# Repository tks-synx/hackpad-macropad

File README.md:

# hackpad-macropad

## Design Renders & Screenshots

### Macropad Design (Fusion)

(Was not able to get the actual models for keycaps, switches, the OLED, rotator or MCU in Fusion)

### 3D Case Design (Fusion)

### Circuit Schematic (KiCad)

### PCB Layout (KiCad)

## Bill of Materials (BOM)
* [1]x Seeed XIAO RP2040 microcontroller
* [10]x MX-style mechanical switches
* [10]x Blank DSA keycaps
* [1]x 0.91” 128×32 OLED display 
* [1]x EC11 rotary encoders
* [4]x M3×16mm screws
* [4]x M3×5×4mm heatset inserts 
* 3D Printing Filament (PLA/PETG) In colour if possible

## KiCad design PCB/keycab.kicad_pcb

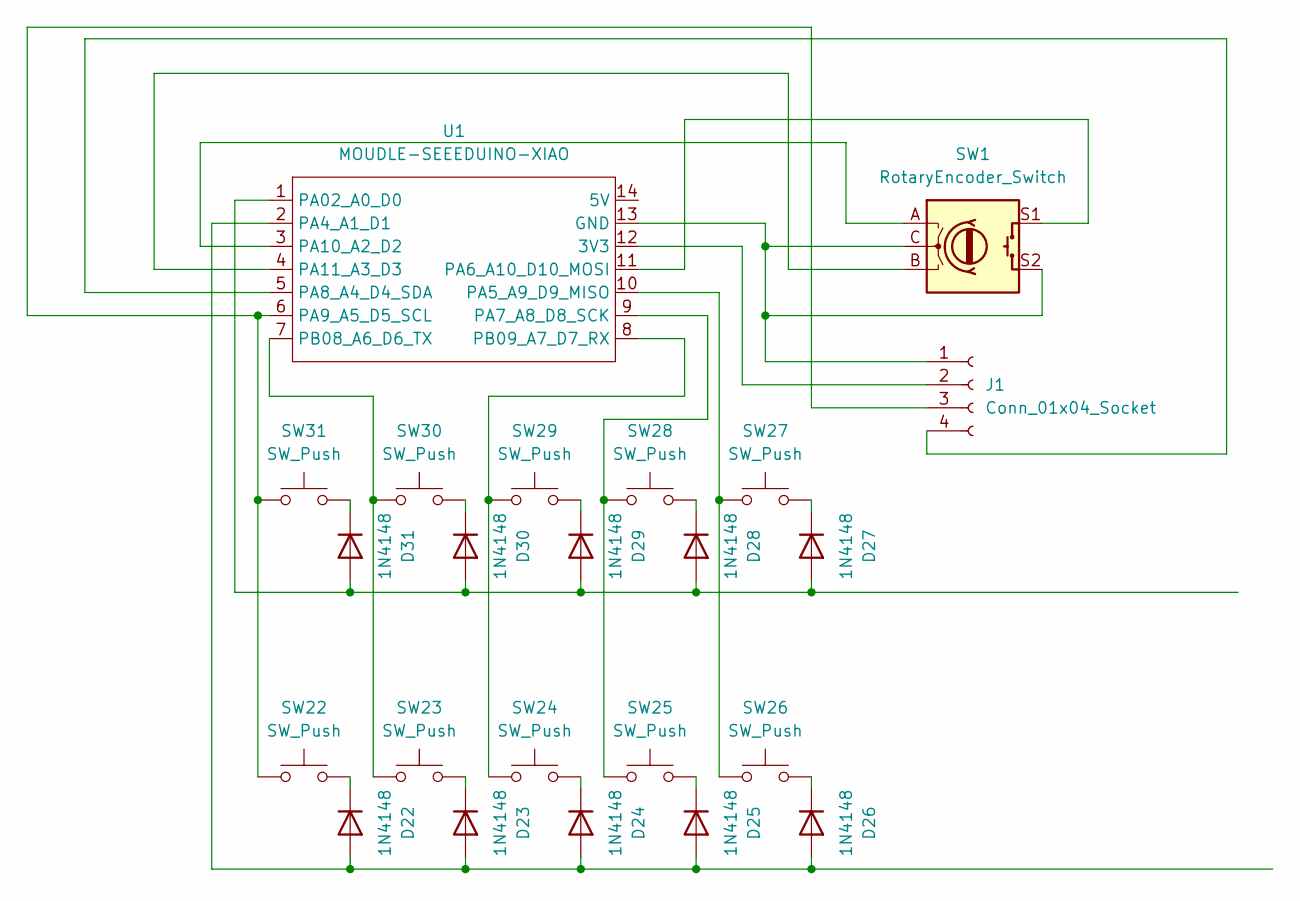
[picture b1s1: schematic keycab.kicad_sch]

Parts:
D22, D23, D24, D25, D26, D27, D28, D29, D30, D31: 1N4148; D_DO-35_SOD27_P7.62mm_Horizontal
J1: Conn_01x04_Socket; PinHeader_1x04_P2.54mm_Vertical
SW1: RotaryEncoder_Switch; RotaryEncoder_Alps_EC11E-Switch_Vertical_H20mm
SW22, SW23, SW24, SW25, SW26, SW27, SW28, SW29, SW30, SW31: SW_Push; SW_Cherry_MX_1.00u_PCB
U1: MOUDLE-SEEEDUINO-XIAO; XIAO-Generic-Hybrid-14P-2.54-21X17.8MM

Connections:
unnamed: D22.2 (A), D23.2 (A), D24.2 (A), D25.2 (A), D26.2 (A), U1.2 (PA4_A1_D1)
unnamed: D22.1 (K), SW22.2
unnamed: D23.1 (K), SW23.2
unnamed: D24.1 (K), SW24.2
unnamed: D25.1 (K), SW25.2
unnamed: D26.1 (K), SW26.2
unnamed: D27.2 (A), D28.2 (A), D29.2 (A), D30.2 (A), D31.2 (A), U1.1 (PA02_A0_D0)
unnamed: D27.1 (K), SW27.2
unnamed: D28.1 (K), SW28.2
unnamed: D29.1 (K), SW29.2
unnamed: D30.1 (K), SW30.2
unnamed: D31.1 (K), SW31.2
unnamed: J1.1, SW1.C, SW1.S2, U1.13 (GND)
unnamed: J1.2, U1.12 (3V3)
unnamed: J1.3, SW22.1, SW31.1, U1.6 (PA9_A5_D5_SCL)
unnamed: J1.4, U1.5 (PA8_A4_D4_SDA)
unnamed: SW26.1, SW27.1, U1.10 (PA5_A9_D9_MISO)
unnamed: SW1.S1, U1.11 (PA6_A10_D10_MOSI)
unnamed: SW25.1, SW28.1, U1.9 (PA7_A8_D8_SCK)
unnamed: SW1.A, U1.3 (PA10_A2_D2)
unnamed: SW1.B, U1.4 (PA11_A3_D3)
unnamed: SW23.1, SW30.1, U1.7 (PB08_A6_D6_TX)
unnamed: SW24.1, SW29.1, U1.8 (PB09_A7_D7_RX)

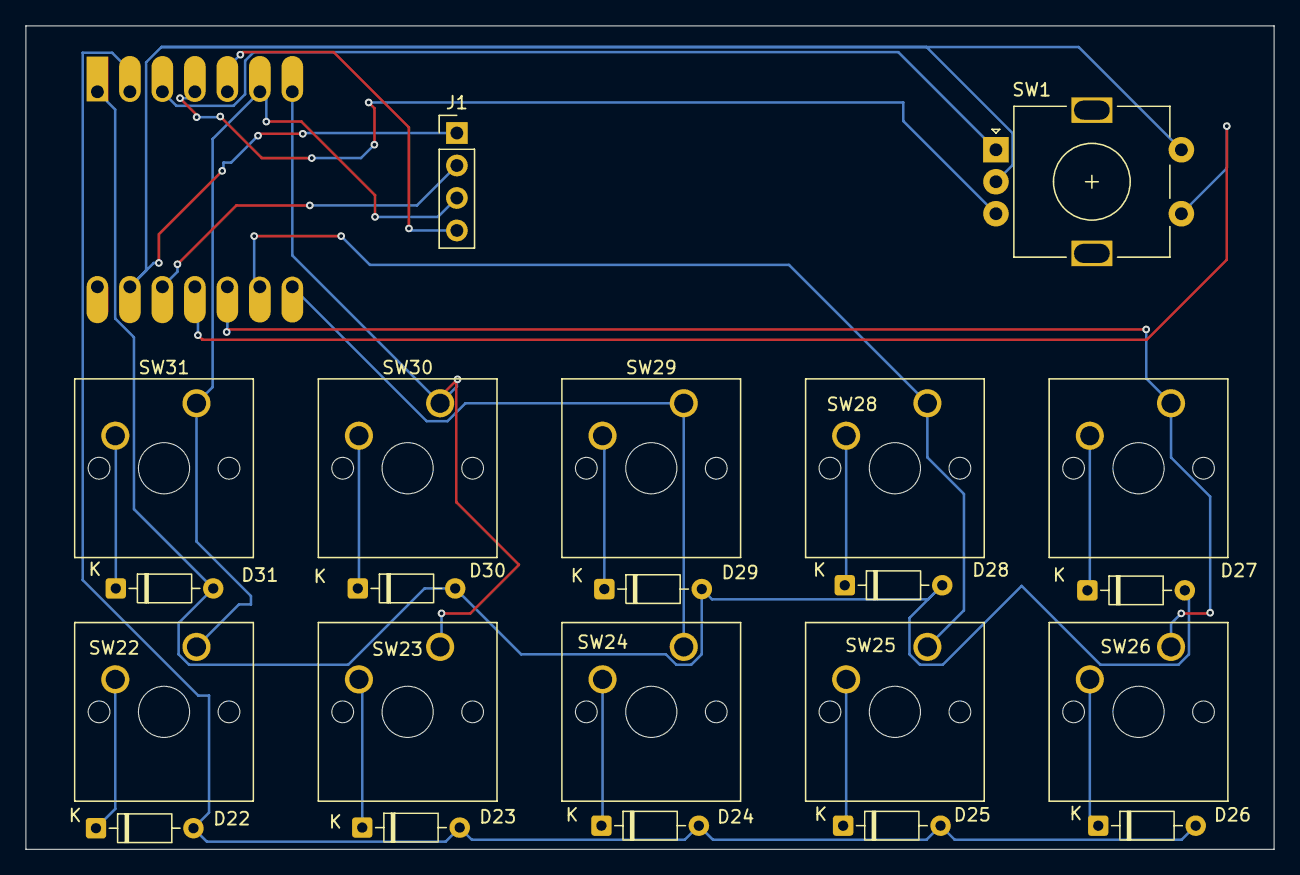
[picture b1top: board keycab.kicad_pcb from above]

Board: 2 copper layers, 97.6 x 64.4 mm, 23 parts (1 on the bottom side), 23 nets.

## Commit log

2026-06-08 feat: successfully compiled macropad layout firmware
2026-06-08 docs: fix readme image paths and finalize submission assets
2026-06-08 Fix image links in README.md
2026-06-08 docs: fix markdown image filename spacing
2026-06-09 Add empty notes.md
    Create an empty notes.md placeholder file to reserve a location for project notes and future documentation.
